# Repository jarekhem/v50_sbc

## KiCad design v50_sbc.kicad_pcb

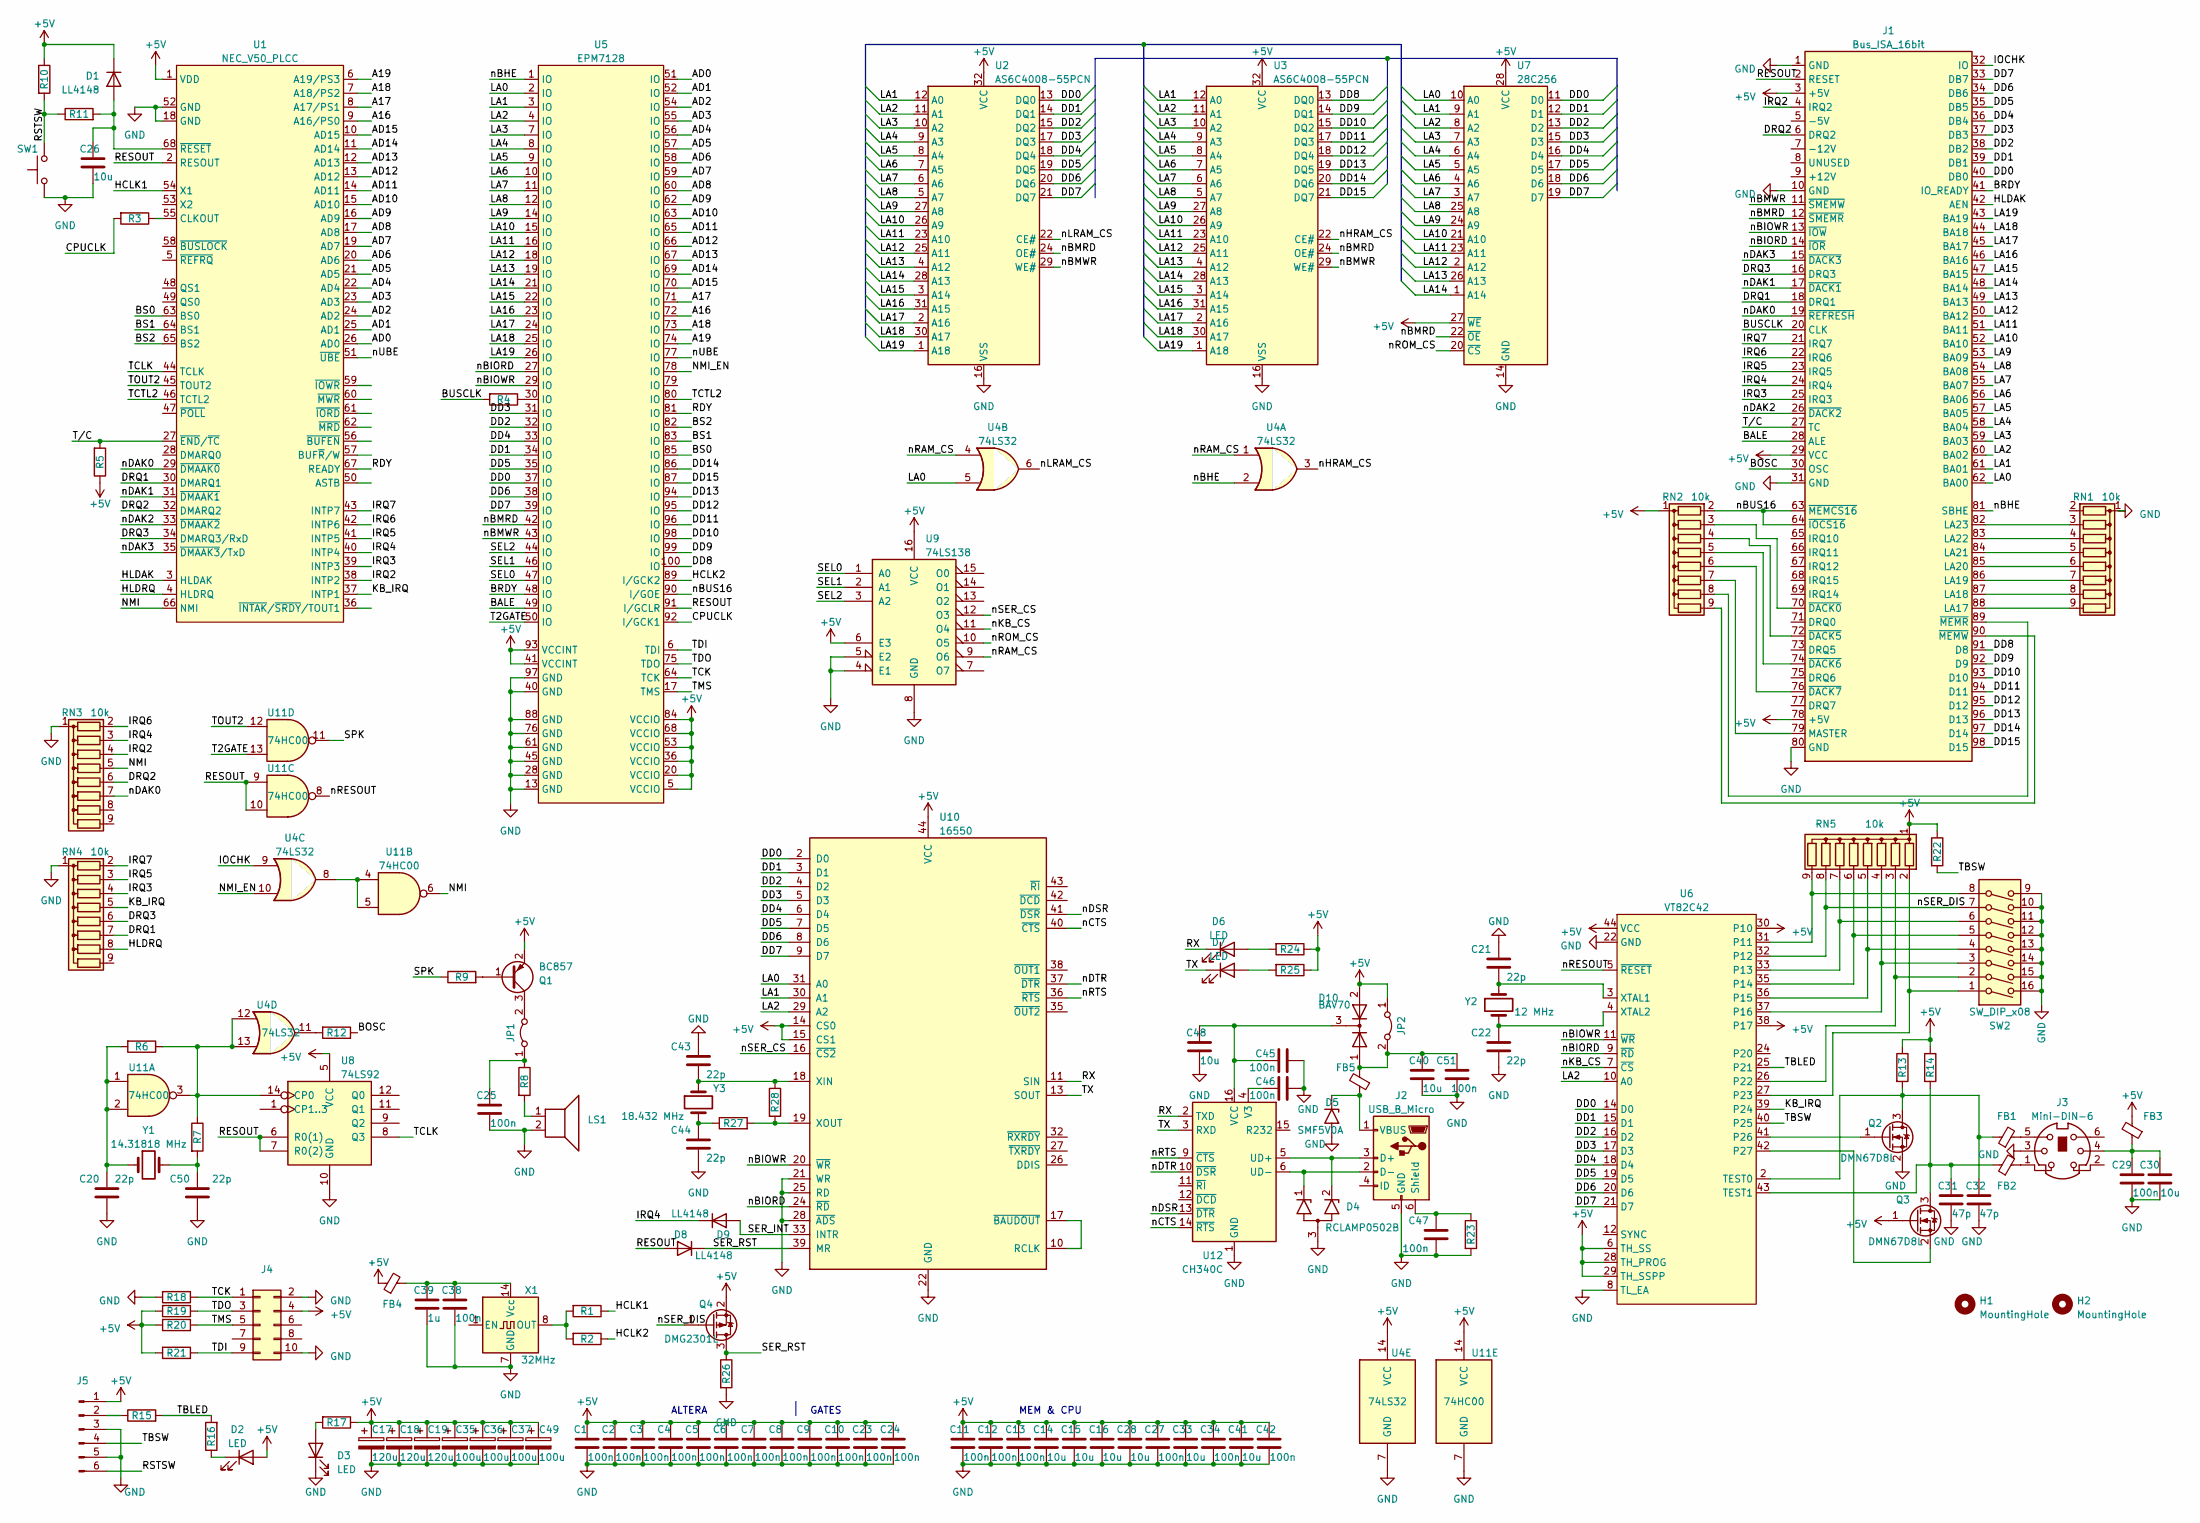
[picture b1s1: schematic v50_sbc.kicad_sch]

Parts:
C1, C2, C3, C4, C5, C6, C7, C8, C9, C10, C11, C12, C13, C23, C24, C25, C27, C29, C34, C38, C42, C45, C46, C47, C51: 100n; C_0603_1608Metric
C14, C15, C16, C28, C30, C33, C40, C41, C48: 10u; C_0805_2012Metric
C17, C18, C19: 120u; CP_Radial_D6.3mm_P2.50mm
C20, C21, C22, C43, C44, C50: 22p; C_0603_1608Metric
C26: 10u; C_1206_3216Metric
C31, C32: 47p; C_0603_1608Metric
C35, C36, C37, C49: 100u; CP_EIA-7343-31_Kemet-D
C39: 1u; C_0603_1608Metric
D1, D8, D9: LL4148; D_MiniMELF
D2, D3, D6, D7: LED; LED_1206_3216Metric
D4: RCLAMP0502B; SOT-416
D5: SMF5V0A; D_SMF
D10: BAV70; SOT-23
FB1, FB2, FB4: FerriteBead_Small; R_0603_1608Metric
FB3, FB5: FerriteBead_Small; R_0805_2012Metric
H1, H2: MountingHole; m3 keystone angle terminal
J1: Bus_ISA_16bit; BUS_AT
J2: USB_B_Micro; USB_Micro-B_TUB
J3: Mini-DIN-6; Connector_Mini-DIN_Female_6Pin_2rows
J4: Conn_02x05_Odd_Even; PinHeader_2x05_P2.54mm_Vertical
J5: Conn_01x06_Pin; PinHeader_1x06_P2.54mm_Horizontal
JP1, JP2: Jumper_2_Bridged; PinHeader_1x02_P2.54mm_Vertical
LS1: Speaker; MagneticBuzzer_ProSignal_ABT-410-RC
Q1: BC857; SOT-23
Q2, Q3: DMN67D8L; SOT-23
Q4: DMG2301L; SOT-23
R1, R3, R4, R12: 33; R_0603_1608Metric
R2, R5, R9, R13, R16, R17, R18, R19, R20, R21, R23, R24, R25, R26: 1k; R_0603_1608Metric
R6, R28: 2.2M; R_0603_1608Metric
R7, R27: 2k2; R_0603_1608Metric
R8, R15: 100; R_0805_2012Metric
R10: 100k; R_0603_1608Metric
R11: 470; R_0603_1608Metric
R14: 4k7; R_0603_1608Metric
R22: 10k; R_0603_1608Metric
RN1, RN2, RN3, RN4, RN5: 10k; R_Array_SIP9
SW1: SW_Push; SW_PUSH_6mm
SW2: SW_DIP_x08; SW_DIP_SPSTx08_Piano_10.8x21.88mm_W7.62mm_P2.54mm
U1: NEC_V50_PLCC; PLCC-68_THT-Socket
U2, U3: AS6C4008-55PCN; SSOP-32_11.305x20.495mm_P1.27mm
U4: 74LS32; SOIC-14_3.9x8.7mm_P1.27mm
U5: EPM7128; PQFP-100_14x20mm_P0.65mm
U6: VT82C42; PLCC-44_THT-Socket
U7: 28C256; DIP-28_W15.24mm_Socket
U8: 74LS92; SOIC-14_3.9x8.7mm_P1.27mm
U9: 74LS138; SOIC-16_3.9x9.9mm_P1.27mm
U10: 16550; PLCC-44_THT-Socket
U11: 74HC00; SOIC-14_3.9x8.7mm_P1.27mm
U12: CH340C; SOIC-16_3.9x9.9mm_P1.27mm
X1: 32MHz; Oscillator_DIP-14_LargePads
Y1: 14.31818 MHz; Crystal_HC18-U_Vertical
Y2: 12 MHz; Crystal_HC18-U_Vertical
Y3: 18.432 MHz; Crystal_HC18-U_Vertical

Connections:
+5V: C1.1, C2.1, C3.1, C4.1, C5.1, C6.1, C7.1, C8.1, C9.1, C10.1, C11.1, C12.1, C13.1, C14.1, C15.1, C16.1, C17.1, C18.1, C19.1, C23.1, C24.1, C27.1, C28.1, C33.1, C34.1, C35.1, C36.1, C37.1, C41.1, C42.1, C49.1, D1.1 (K), D2.2 (A), D10.2 (A), FB3.2, FB4.1, J1.3 (+5V), J1.29 (VCC), J1.78 (+5V), J4.4, J5.1, JP2.1 (A), Q1.2 (E), Q3.1 (G), Q4.2 (S), R5.1, R10.1, R13.1, R14.1, R17.1, R19.2, R20.2, R21.2, R22.1, R24.1, R25.1, RN2.1 (common), RN5.1 (common), U1.1 (VDD), U2.32 (VCC), U3.32 (VCC), U4.14 (VCC), U5.5 (VCCIO), U5.20 (VCCIO), U5.36 (VCCIO), U5.41 (VCCINT), U5.53 (VCCIO), U5.68 (VCCIO), U5.84 (VCCIO), U5.93 (VCCINT), U6.6 (TH_SS), U6.28 (TH_PROG), U6.29 (TH_SSPP), U6.30 (P10), U6.38 (P17), U6.44 (VCC), U7.27 (~WE), U7.28 (VCC), U8.5 (VCC), U9.6 (E3), U9.16 (VCC), U10.14 (CS0), U10.15 (CS1), U10.44 (VCC), U11.14 (VCC)
/A16: U1.9 (A16/PS0), U5.72 (IO)
/A17: U1.8 (A17/PS1), U5.71 (IO)
/A18: U1.7 (A18/PS2), U5.73 (IO)
/A19: U1.6 (A19/PS3), U5.74 (IO)
/AD0: U1.26 (AD0), U5.51 (IO)
/AD1: U1.25 (AD1), U5.52 (IO)
/AD2: U1.24 (AD2), U5.54 (IO)
/AD3: U1.23 (AD3), U5.55 (IO)
/AD4: U1.22 (AD4), U5.56 (IO)
/AD5: U1.21 (AD5), U5.57 (IO)
/AD6: U1.20 (AD6), U5.58 (IO)
/AD7: U1.19 (AD7), U5.59 (IO)
/AD8: U1.17 (AD8), U5.60 (IO)
/AD9: U1.16 (AD9), U5.62 (IO)
/AD10: U1.15 (AD10), U5.63 (IO)
/AD11: U1.14 (AD11), U5.65 (IO)
/AD12: U1.13 (AD12), U5.66 (IO)
/AD13: U1.12 (AD13), U5.67 (IO)
/AD14: U1.11 (AD14), U5.69 (IO)
/AD15: U1.10 (AD15), U5.70 (IO)
/BALE: J1.28 (ALE), U5.49 (IO)
/BOSC: J1.30 (OSC), R12.1
/BRDY: J1.41 (IO_READY), U5.48 (IO)
/BS0: U1.63 (BS0), U5.85 (IO)
/BS1: U1.64 (BS1), U5.83 (IO)
/BS2: U1.65 (BS2), U5.82 (IO)
/BUSCLK: J1.20 (CLK), R4.2
/CPUCLK: R3.2, U5.92 (I/GCK1)
/DD0: J1.40 (DB0), U2.13 (DQ0), U5.37 (IO), U6.14 (D0), U7.11 (D0), U10.2 (D0)
/DD1: J1.39 (DB1), U2.14 (DQ1), U5.34 (IO), U6.15 (D1), U7.12 (D1), U10.3 (D1)
/DD2: J1.38 (DB2), U2.15 (DQ2), U5.32 (IO), U6.16 (D2), U7.13 (D2), U10.4 (D2)
/DD3: J1.37 (DB3), U2.17 (DQ3), U5.31 (IO), U6.17 (D3), U7.15 (D3), U10.5 (D3)
/DD4: J1.36 (DB4), U2.18 (DQ4), U5.33 (IO), U6.18 (D4), U7.16 (D4), U10.6 (D4)
/DD5: J1.35 (DB5), U2.19 (DQ5), U5.35 (IO), U6.19 (D5), U7.17 (D5), U10.7 (D5)
/DD6: J1.34 (DB6), U2.20 (DQ6), U5.38 (IO), U6.20 (D6), U7.18 (D6), U10.8 (D6)
/DD7: J1.33 (DB7), U2.21 (DQ7), U5.39 (IO), U6.21 (D7), U7.19 (D7), U10.9 (D7)
/DD8: J1.91 (D8), U3.13 (DQ0), U5.100 (IO)
/DD9: J1.92 (D9), U3.14 (DQ1), U5.99 (IO)
/DD10: J1.93 (D10), U3.15 (DQ2), U5.98 (IO)
/DD11: J1.94 (D11), U3.17 (DQ3), U5.96 (IO)
/DD12: J1.95 (D12), U3.18 (DQ4), U5.95 (IO)
/DD13: J1.96 (D13), U3.19 (DQ5), U5.94 (IO)
/DD14: J1.97 (D14), U3.20 (DQ6), U5.86 (IO)
/DD15: J1.98 (D15), U3.21 (DQ7), U5.87 (IO)
/DRQ1: J1.18 (DRQ1), RN4.7 (R6), U1.30 (DMARQ1)
/DRQ2: J1.6 (DRQ2), RN3.6 (R5), U1.32 (DMARQ2)
/DRQ3: J1.16 (DRQ3), RN4.6 (R5), U1.34 (DMARQ3/RxD)
/HCLK1: R1.1, U1.54 (X1)
/HCLK2: R2.1, U5.89 (I/GCK2)
/HLDAK: J1.42 (AEN), U1.3 (HLDAK)
/HLDRQ: RN4.8 (R7), U1.4 (HLDRQ)
/IOCHK: J1.32 (IO), U4.9
/IRQ2: J1.4 (IRQ2), RN3.4 (R3), U1.38 (INTP2)
/IRQ3: J1.25 (IRQ3), RN4.4 (R3), U1.39 (INTP3)
/IRQ4: D9.1 (K), J1.24 (IRQ4), RN3.3 (R2), U1.40 (INTP4)
/IRQ5: J1.23 (IRQ5), RN4.3 (R2), U1.41 (INTP5)
/IRQ6: J1.22 (IRQ6), RN3.2 (R1), U1.42 (INTP6)
/IRQ7: J1.21 (IRQ7), RN4.2 (R1), U1.43 (INTP7)
/KB_IRQ: RN4.5 (R4), U1.37 (INTP1), U6.39 (P24)
/LA0: J1.62 (BA00), U4.5, U5.2 (IO), U7.10 (A0), U10.31 (A0)
/LA1: J1.61 (BA01), U2.12 (A0), U3.12 (A0), U5.3 (IO), U7.9 (A1), U10.30 (A1)
/LA2: J1.60 (BA02), U2.11 (A1), U3.11 (A1), U5.4 (IO), U6.10 (A0), U7.8 (A2), U10.29 (A2)
/LA3: J1.59 (BA03), U2.10 (A2), U3.10 (A2), U5.7 (IO), U7.7 (A3)
/LA4: J1.58 (BA04), U2.9 (A3), U3.9 (A3), U5.8 (IO), U7.6 (A4)
/LA5: J1.57 (BA05), U2.8 (A4), U3.8 (A4), U5.9 (IO), U7.5 (A5)
/LA6: J1.56 (BA06), U2.7 (A5), U3.7 (A5), U5.10 (IO), U7.4 (A6)
/LA7: J1.55 (BA07), U2.6 (A6), U3.6 (A6), U5.11 (IO), U7.3 (A7)
/LA8: J1.54 (BA08), U2.5 (A7), U3.5 (A7), U5.12 (IO), U7.25 (A8)
/LA9: J1.53 (BA09), U2.27 (A8), U3.27 (A8), U5.14 (IO), U7.24 (A9)
/LA10: J1.52 (BA10), U2.26 (A9), U3.26 (A9), U5.15 (IO), U7.21 (A10)
/LA11: J1.51 (BA11), U2.23 (A10), U3.23 (A10), U5.16 (IO), U7.23 (A11)
/LA12: J1.50 (BA12), U2.25 (A11), U3.25 (A11), U5.18 (IO), U7.2 (A12)
/LA13: J1.49 (BA13), U2.4 (A12), U3.4 (A12), U5.19 (IO), U7.26 (A13)
/LA14: J1.48 (BA14), U2.28 (A13), U3.28 (A13), U5.21 (IO), U7.1 (A14)
/LA15: J1.47 (BA15), U2.3 (A14), U3.3 (A14), U5.22 (IO)
/LA16: J1.46 (BA16), U2.31 (A15), U3.31 (A15), U5.23 (IO)
/LA17: J1.45 (BA17), U2.2 (A16), U3.2 (A16), U5.24 (IO)
/LA18: J1.44 (BA18), U2.30 (A17), U3.30 (A17), U5.25 (IO)
/LA19: J1.43 (BA19), U2.1 (A18), U3.1 (A18), U5.26 (IO)
/NMI: RN3.5 (R4), U1.66 (NMI), U11.6
/NMI_EN: U4.10, U5.78 (IO)
/RDY: U1.67 (READY), U5.81 (IO)
/RESOUT: D8.2 (A), J1.2 (RESET), U1.2 (RESOUT), U5.91 (I/GCLR), U8.6 (R0(1)), U8.7 (R0(2)), U11.9, U11.10
/RSTSW: J5.6, R10.2, R11.1, SW1.2
/RX: D6.1 (K), U10.11 (SIN), U12.2 (TXD)
/SEL0: U5.47 (IO), U9.1 (A0)
/SEL1: U5.46 (IO), U9.2 (A1)
/SEL2: U5.44 (IO), U9.3 (A2)
/SER_INT: D9.2 (A), U10.33 (INTR)
/SER_RST: D8.1 (K), Q4.3 (D), R26.1, U10.39 (MR)
/SPK: R9.1, U11.11
/T2GATE: U5.50 (IO), U11.13
/TBLED: R15.2, R16.2, U6.25 (P21)
/TBSW: J5.4, R22.2, U6.40 (P25)
/TCK: J4.1, R18.1, U5.64 (TCK)
/TCLK: U1.44 (TCLK), U8.8 (Q3)
/TCTL2: U1.46 (TCTL2), U5.80 (IO)
/TDI: J4.9, R21.1, U5.6 (TDI)
/TDO: J4.3, R19.1, U5.75 (TDO)
/TMS: J4.5, R20.1, U5.17 (TMS)
/TOUT2: U1.45 (TOUT2), U11.12
/TX: D7.1 (K), U10.13 (SOUT), U12.3 (RXD)
/T/C: J1.27 (TC), R5.2, U1.27 (~END/~TC)
/nBHE: J1.81 (SBHE), U4.2, U5.1 (IO)
/nBIORD: J1.14 (~IOR), U5.27 (IO), U6.9 (~RD), U10.24 (~RD)
/nBIOWR: J1.13 (~IOW), U5.29 (IO), U6.11 (~WR), U10.20 (~WR)
/nBMRD: J1.12 (~SMEMR), U2.24 (OE#), U3.24 (OE#), U5.42 (IO), U7.22 (~OE)
/nBMWR: J1.11 (~SMEMW), U2.29 (WE#), U3.29 (WE#), U5.43 (IO)
/nBUS16: J1.63 (~MEMCS16), J1.64 (~IOCS16), RN2.2 (R1), U5.90 (I/GOE)
/nCTS: U10.40 (~CTS), U12.14 (~RTS)
/nDAK0: J1.19 (~REFRESH), RN3.7 (R6), U1.29 (~DMAAK0)
/nDAK1: J1.17 (~DACK1), U1.31 (~DMAAK1)
/nDAK2: J1.26 (~DACK2), U1.33 (~DMAAK2)
/nDAK3: J1.15 (~DACK3), U1.35 (~DMAAK3/TxD)
/nDSR: U10.41 (~DSR), U12.13 (~DTR)
/nDTR: U10.37 (~DTR), U12.10 (~DSR)
/nHRAM_CS: U3.22 (CE#), U4.3
/nKB_CS: U6.7 (~CS), U9.11 (O4)
/nLRAM_CS: U2.22 (CE#), U4.6
/nRAM_CS: U4.1, U4.4, U9.9 (O6)
/nRESOUT: U6.5 (~RESET), U11.8
/nROM_CS: U7.20 (~CS), U9.10 (O5)
/nRTS: U10.36 (~RTS), U12.9 (~CTS)
/nSER_CS: U9.12 (O3), U10.16 (~CS2)
/nSER_DIS: Q4.1 (G), RN5.8 (R7), SW2.7, U6.32 (P12)
/nUBE: U1.51 (~UBE), U5.77 (IO)
GND: C1.2, C2.2, C3.2, C4.2, C5.2, C6.2, C7.2, C8.2, C9.2, C10.2, C11.2, C12.2, C13.2, C14.2, C15.2, C16.2, C17.2, C18.2, C19.2, C20.1, C21.2, C22.1, C23.2, C24.2, C25.2, C26.2, C27.2, C28.2, C29.2, C30.2, C31.2, C32.2, C33.2, C34.2, C35.2, C36.2, C37.2, C38.2, C39.2, C40.2, C41.2, C42.2, C43.2, C44.1, C45.2, C46.2, C47.1, C48.2, C49.2, C50.1, C51.1, D3.1 (K), D4.3 (A), D5.2 (A2), J1.1 (GND), J1.10 (GND), J1.31 (GND), J1.80 (GND), J2.5 (GND), J3.3, J4.2, J4.10, J5.3, J5.5, LS1.2, Q2.2 (S), R18.2, R23.2, R26.2, RN1.1 (common), RN3.1 (common), RN4.1 (common), SW1.1, SW2.9, SW2.10, SW2.11, SW2.12, SW2.13, SW2.14, SW2.15, SW2.16, U1.18 (GND), U1.52 (GND), U2.16 (VSS), U3.16 (VSS), U4.7 (GND), U5.13 (GND), U5.28 (GND), U5.40 (GND), U5.45 (GND), U5.61 (GND), U5.76 (GND), U5.88 (GND), U5.97 (GND), U6.8 (TL_EA), U6.22 (GND), U7.14 (GND), U8.10 (GND), U9.4 (E1), U9.5 (E2), U9.8 (GND), U10.21 (WR), U10.22 (GND), U10.25 (RD), U10.28 (~ADS), U11.7 (GND), U12.1 (GND), X1.7 (GND)
unnamed: C20.2, R6.2, U11.1, U11.2, Y1.1
unnamed: C29.1, C30.1, FB3.1, J3.4
unnamed: C44.2, R27.1, Y3.2
unnamed: C50.2, R7.2, Y1.2
unnamed: C26.1, D1.2 (A), R11.2, U1.68 (~RESET)
unnamed: D2.1 (K), R16.1
unnamed: D3.2 (A), R17.2
unnamed: D4.1 (K1), J2.2 (D-), U12.6 (UD-)
unnamed: D4.2 (K2), J2.3 (D+), U12.5 (UD+)
unnamed: D5.1 (A1), FB5.1, J2.1 (VBUS)
unnamed: D6.2 (A), R24.2
unnamed: D7.2 (A), R25.2
unnamed: C45.1, C48.1, D10.3 (K), U12.16 (VCC)
unnamed: FB1.2, J3.5
unnamed: FB2.2, J3.1
unnamed: J1.88 (LA17), RN1.9 (R8)
unnamed: J1.87 (LA18), RN1.8 (R7)
unnamed: J1.86 (LA19), RN1.7 (R6)
unnamed: J1.85 (LA20), RN1.6 (R5)
unnamed: J1.84 (LA21), RN1.5 (R4)
unnamed: J1.83 (LA22), RN1.4 (R3)
unnamed: J1.82 (LA23), RN1.3 (R2)
unnamed: J1.79 (MASTER), RN2.7 (R6)
unnamed: J1.70 (~DACK0), RN2.3 (R2)
unnamed: J1.72 (~DACK5), RN2.4 (R3)
unnamed: J1.74 (~DACK6), RN2.5 (R4)
unnamed: J1.76 (~DACK7), RN2.6 (R5)
unnamed: J1.89 (~MEMR), RN2.8 (R7)
unnamed: J1.90 (~MEMW), RN2.9 (R8)
unnamed: C47.2, J2.6 (Shield), R23.1
unnamed: J5.2, R15.1
unnamed: C25.1, JP1.1 (A), R8.1
unnamed: JP1.2 (B), Q1.3 (C)
unnamed: C40.1, C51.2, D10.1 (A), FB5.2, JP2.2 (B)
unnamed: LS1.1, R8.2
unnamed: Q1.1 (B), R9.2
unnamed: C32.1, FB1.1, Q2.3 (D), R13.2, U6.2 (TEST0)
unnamed: Q2.1 (G), U6.41 (P26)
unnamed: C31.1, FB2.1, Q3.3 (D), R14.2, U6.43 (TEST1)
unnamed: Q3.2 (S), U6.42 (P27)
unnamed: R4.1, U5.30 (IO)
unnamed: R12.2, U4.11
unnamed: RN5.2 (R1), SW2.1, U6.27 (P23)
unnamed: RN5.3 (R2), SW2.2, U6.26 (P22)
unnamed: RN5.4 (R3), SW2.3, U6.37 (P16)
unnamed: RN5.5 (R4), SW2.4, U6.36 (P15)
unnamed: RN5.6 (R5), SW2.5, U6.35 (P14)
unnamed: RN5.7 (R6), SW2.6, U6.33 (P13)
unnamed: RN5.9 (R8), SW2.8, U6.31 (P11)
unnamed: R3.1, U1.55 (CLKOUT)
unnamed: C21.1, U6.3 (XTAL1), Y2.1
unnamed: C22.2, U6.4 (XTAL2), Y2.2
unnamed: R6.1, R7.1, U4.12, U4.13, U8.14 (CP0), U11.3
unnamed: U10.10 (RCLK), U10.17 (~BAUDOUT)
unnamed: C43.1, R28.1, U10.18 (XIN), Y3.1
unnamed: R27.2, R28.2, U10.19 (XOUT)
unnamed: U4.8, U11.4, U11.5
unnamed: C46.1, U12.4 (V3)
unnamed: R1.2, R2.2, X1.8 (OUT)
unnamed: C38.1, C39.1, FB4.2, X1.14 (Vcc)

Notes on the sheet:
GATES
ALTERA
MEM & CPU

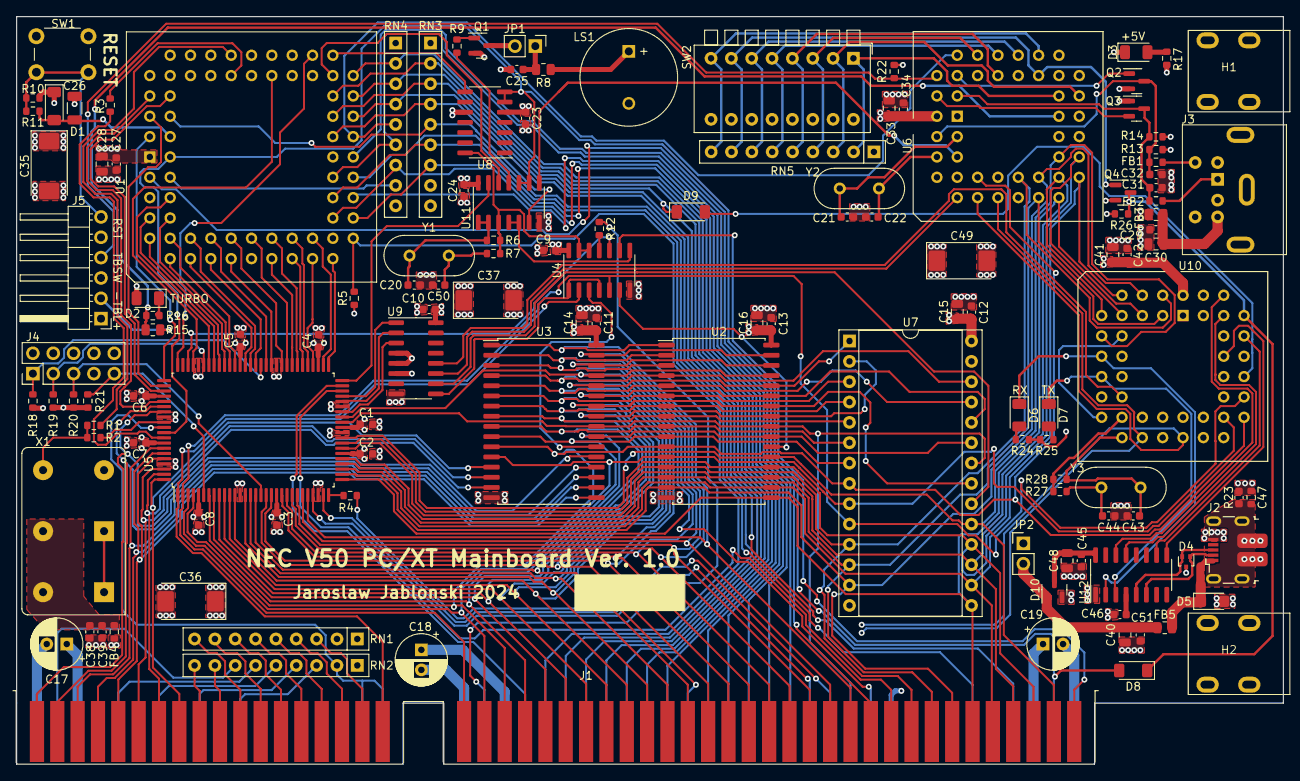
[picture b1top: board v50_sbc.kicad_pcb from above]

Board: 4 copper layers, 158.2 x 93.3 mm, 131 parts (0 on the bottom side), 188 nets.

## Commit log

2025-01-19 Added project files of version 1.0
